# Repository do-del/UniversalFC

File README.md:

# UniversalFC
自制的一些通用航模组件
目前已添加基于STC单片机的无刷电调PCB设计文件，还在打样验证中。

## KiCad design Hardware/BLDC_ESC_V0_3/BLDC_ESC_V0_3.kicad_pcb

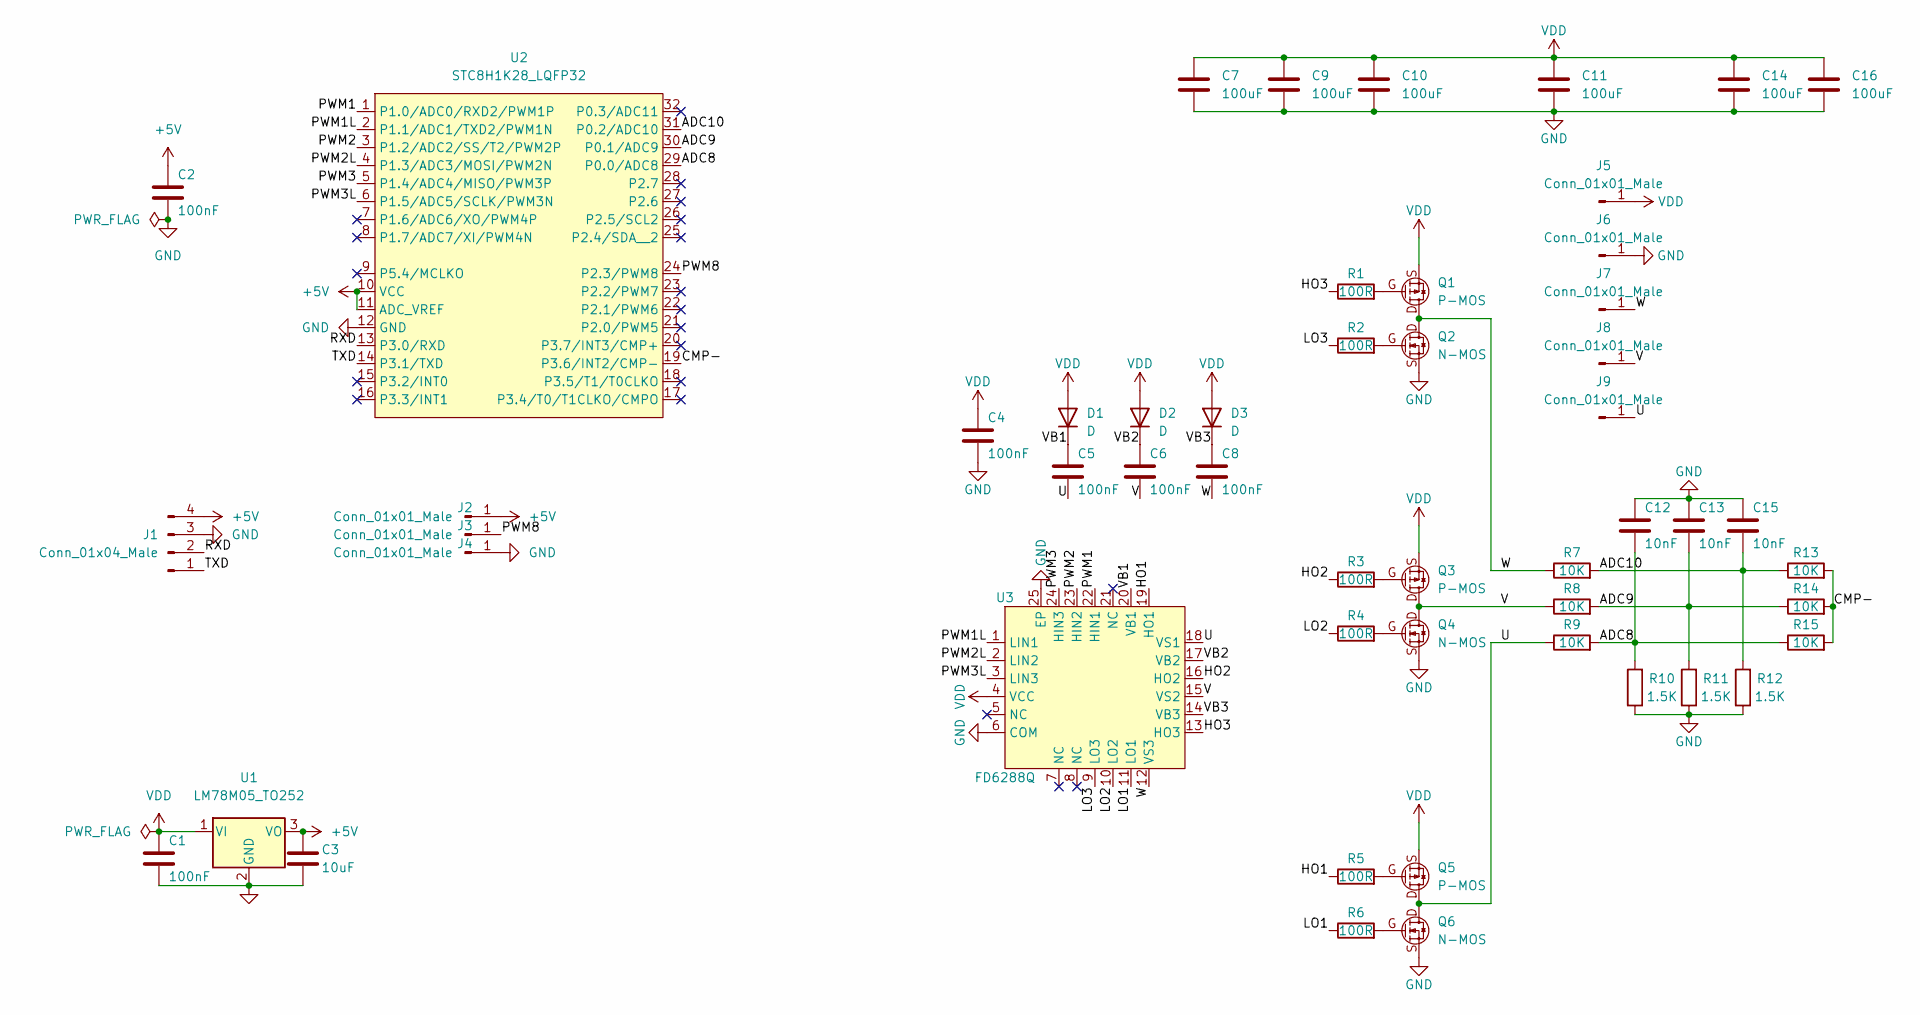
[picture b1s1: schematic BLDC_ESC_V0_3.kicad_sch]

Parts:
C1, C2, C4, C5, C6, C8: 100nF; C_0603_1608Metric_Pad1.08x0.95mm_HandSolder
C3: 10uF; C_0603_1608Metric_Pad1.08x0.95mm_HandSolder
C7, C9, C10, C11, C14, C16: 100uF; C_1210_3225Metric
C12, C13, C15: 10nF; C_0603_1608Metric_Pad1.08x0.95mm_HandSolder
D1, D2, D3: D; D_SOD-323_HandSoldering
J1: Conn_01x04_Male; SH1.0mm_4P_WT
J2, J3, J4, J5, J6, J7, J8, J9: Conn_01x01_Male; PAD_RECT
Q1, Q3, Q5: P-MOS; DFN_3x3_MOS
Q2, Q4, Q6: N-MOS; DFN_3x3_MOS
R1, R2, R3, R4, R5, R6: 100R; R_0603_1608Metric_Pad0.98x0.95mm_HandSolder
R7, R8, R9, R13, R14, R15: 10K; R_0603_1608Metric_Pad0.98x0.95mm_HandSolder
R10, R11, R12: 1.5K; R_0603_1608Metric_Pad0.98x0.95mm_HandSolder
U1: LM78M05_TO252; SOT-89-3
U2: STC8H1K28_LQFP32; QFN-32-1EP_4x4mm_P0.4mm_EP2.65x2.65mm
U3: FD6288Q; QFN-24-1EP_4x4mm_P0.5mm_EP2.6x2.6mm

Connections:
+5V: C2.1, C3.1, J1.4, J2.1, U1.3 (VO), U2.10 (VCC), U2.11 (ADC_VREF)
/ADC8: C12.2, R9.2, R10.2, R15.1, U2.29 (P0.0/ADC8)
/ADC9: C13.2, R8.2, R11.2, R14.1, U2.30 (P0.1/ADC9)
/ADC10: C15.2, R7.2, R12.2, R13.1, U2.31 (P0.2/ADC10)
/CMP-: R13.2, R14.2, R15.2, U2.19 (P3.6/INT2/CMP-)
/HO1: R5.1, U3.19 (HO1)
/HO2: R3.1, U3.16 (HO2)
/HO3: R1.1, U3.13 (HO3)
/LO1: R6.1, U3.11 (LO1)
/LO2: R4.1, U3.10 (LO2)
/LO3: R2.1, U3.9 (LO3)
/PWM1: U2.1 (P1.0/ADC0/RXD2/PWM1P), U3.22 (HIN1)
/PWM1L: U2.2 (P1.1/ADC1/TXD2/PWM1N), U3.1 (LIN1)
/PWM2: U2.3 (P1.2/ADC2/SS/T2/PWM2P), U3.23 (HIN2)
/PWM2L: U2.4 (P1.3/ADC3/MOSI/PWM2N), U3.2 (LIN2)
/PWM3: U2.5 (P1.4/ADC4/MISO/PWM3P), U3.24 (HIN3)
/PWM3L: U2.6 (P1.5/ADC5/SCLK/PWM3N), U3.3 (LIN3)
/PWM8: J3.1, U2.24 (P2.3/PWM8)
/RXD: J1.2, U2.13 (P3.0/RXD)
/TXD: J1.1, U2.14 (P3.1/TXD)
/U: C5.2, J9.1, Q5.D, Q6.D, R9.1, U3.18 (VS1)
/V: C6.2, J8.1, Q3.D, Q4.D, R8.1, U3.15 (VS2)
/VB1: C5.1, D1.1 (K), U3.20 (VB1)
/VB2: C6.1, D2.1 (K), U3.17 (VB2)
/VB3: C8.1, D3.1 (K), U3.14 (VB3)
/W: C8.2, J7.1, Q1.D, Q2.D, R7.1, U3.12 (VS3)
GND: C1.2, C2.2, C3.2, C4.2, C7.2, C9.2, C10.2, C11.2, C12.1, C13.1, C14.2, C15.1, C16.2, J1.3, J4.1, J6.1, Q2.S, Q4.S, Q6.S, R10.1, R11.1, R12.1, U1.2 (GND), U2.12 (GND), U3.6 (COM), U3.25 (EP)
unnamed: Q1.G, R1.2
unnamed: Q2.G, R2.2
unnamed: Q3.G, R3.2
unnamed: Q4.G, R4.2
unnamed: Q5.G, R5.2
unnamed: Q6.G, R6.2
VDD: C1.1, C4.1, C7.1, C9.1, C10.1, C11.1, C14.1, C16.1, D1.2 (A), D2.2 (A), D3.2 (A), J5.1, Q1.S, Q3.S, Q5.S, U1.1 (VI), U3.4 (VCC)

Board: 2 copper layers, 52 parts (25 on the bottom side), 34 nets, no tracks yet.

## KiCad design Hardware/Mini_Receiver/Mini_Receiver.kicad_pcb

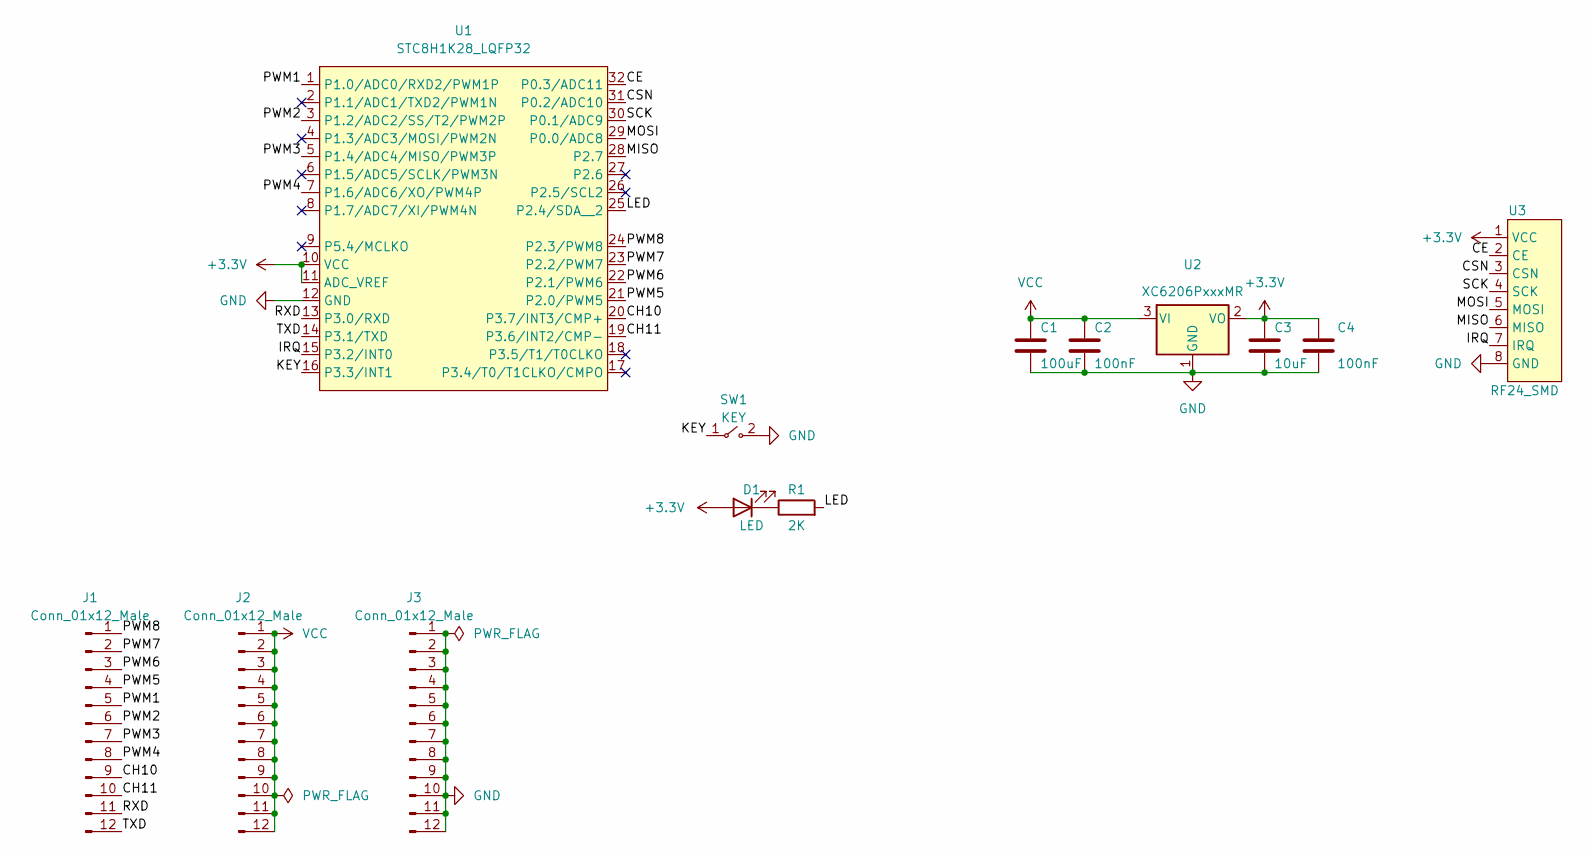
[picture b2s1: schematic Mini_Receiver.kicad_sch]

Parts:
C1: 100uF; C_1210_3225Metric
C2, C4: 100nF; C_0603_1608Metric_Pad1.08x0.95mm_HandSolder
C3: 10uF; C_0603_1608Metric_Pad1.08x0.95mm_HandSolder
D1: LED; LED_0603_1608Metric_Pad1.05x0.95mm_HandSolder
J1, J2, J3: Conn_01x12_Male; PinHeader_1x12_P2.54mm_Vertical
R1: 2K; R_0603_1608Metric_Pad0.98x0.95mm_HandSolder
SW1: KEY; SW_3x4
U1: STC8H1K28_LQFP32; LQFP-32_7x7mm_P0.8mm
U2: XC6206PxxxMR; SOT-23
U3: RF24_SMD

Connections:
+3V3: C3.1, C4.1, D1.2 (A), U1.10 (VCC), U1.11 (ADC_VREF), U2.2 (VO), U3.1 (VCC)
/CE: U1.32 (P0.3/ADC11), U3.2 (CE)
/CH10: J1.9, U1.20 (P3.7/INT3/CMP+)
/CH11: J1.10, U1.19 (P3.6/INT2/CMP-)
/CSN: U1.31 (P0.2/ADC10), U3.3 (CSN)
/IRQ: U1.15 (P3.2/INT0), U3.7 (IRQ)
/KEY: SW1.1 (A), U1.16 (P3.3/INT1)
/LED: R1.2, U1.25 (P2.4/SDA__2)
/MISO: U1.28 (P2.7), U3.6 (MISO)
/MOSI: U1.29 (P0.0/ADC8), U3.5 (MOSI)
/PWM1: J1.5, U1.1 (P1.0/ADC0/RXD2/PWM1P)
/PWM2: J1.6, U1.3 (P1.2/ADC2/SS/T2/PWM2P)
/PWM3: J1.7, U1.5 (P1.4/ADC4/MISO/PWM3P)
/PWM4: J1.8, U1.7 (P1.6/ADC6/XO/PWM4P)
/PWM5: J1.4, U1.21 (P2.0/PWM5)
/PWM6: J1.3, U1.22 (P2.1/PWM6)
/PWM7: J1.2, U1.23 (P2.2/PWM7)
/PWM8: J1.1, U1.24 (P2.3/PWM8)
/RXD: J1.11, U1.13 (P3.0/RXD)
/SCK: U1.30 (P0.1/ADC9), U3.4 (SCK)
/TXD: J1.12, U1.14 (P3.1/TXD)
GND: C1.2, C2.2, C3.2, C4.2, J3.1, J3.2, J3.3, J3.4, J3.5, J3.6, J3.7, J3.8, J3.9, J3.10, J3.11, J3.12, SW1.2 (B), U1.12 (GND), U2.1 (GND), U3.8 (GND)
unnamed: D1.1 (K), R1.1
VCC: C1.1, C2.1, J2.1, J2.2, J2.3, J2.4, J2.5, J2.6, J2.7, J2.8, J2.9, J2.10, J2.11, J2.12, U2.3 (VI)

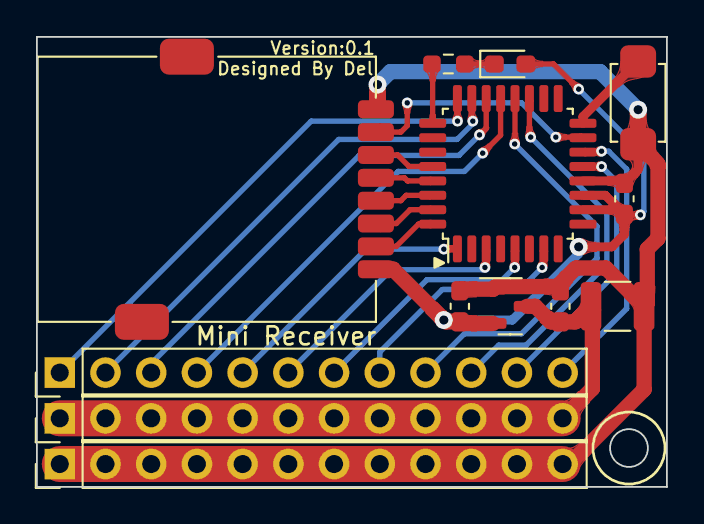
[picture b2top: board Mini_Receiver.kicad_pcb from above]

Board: 2 copper layers, 35.0 x 25.0 mm, 13 parts (0 on the bottom side), 24 nets.

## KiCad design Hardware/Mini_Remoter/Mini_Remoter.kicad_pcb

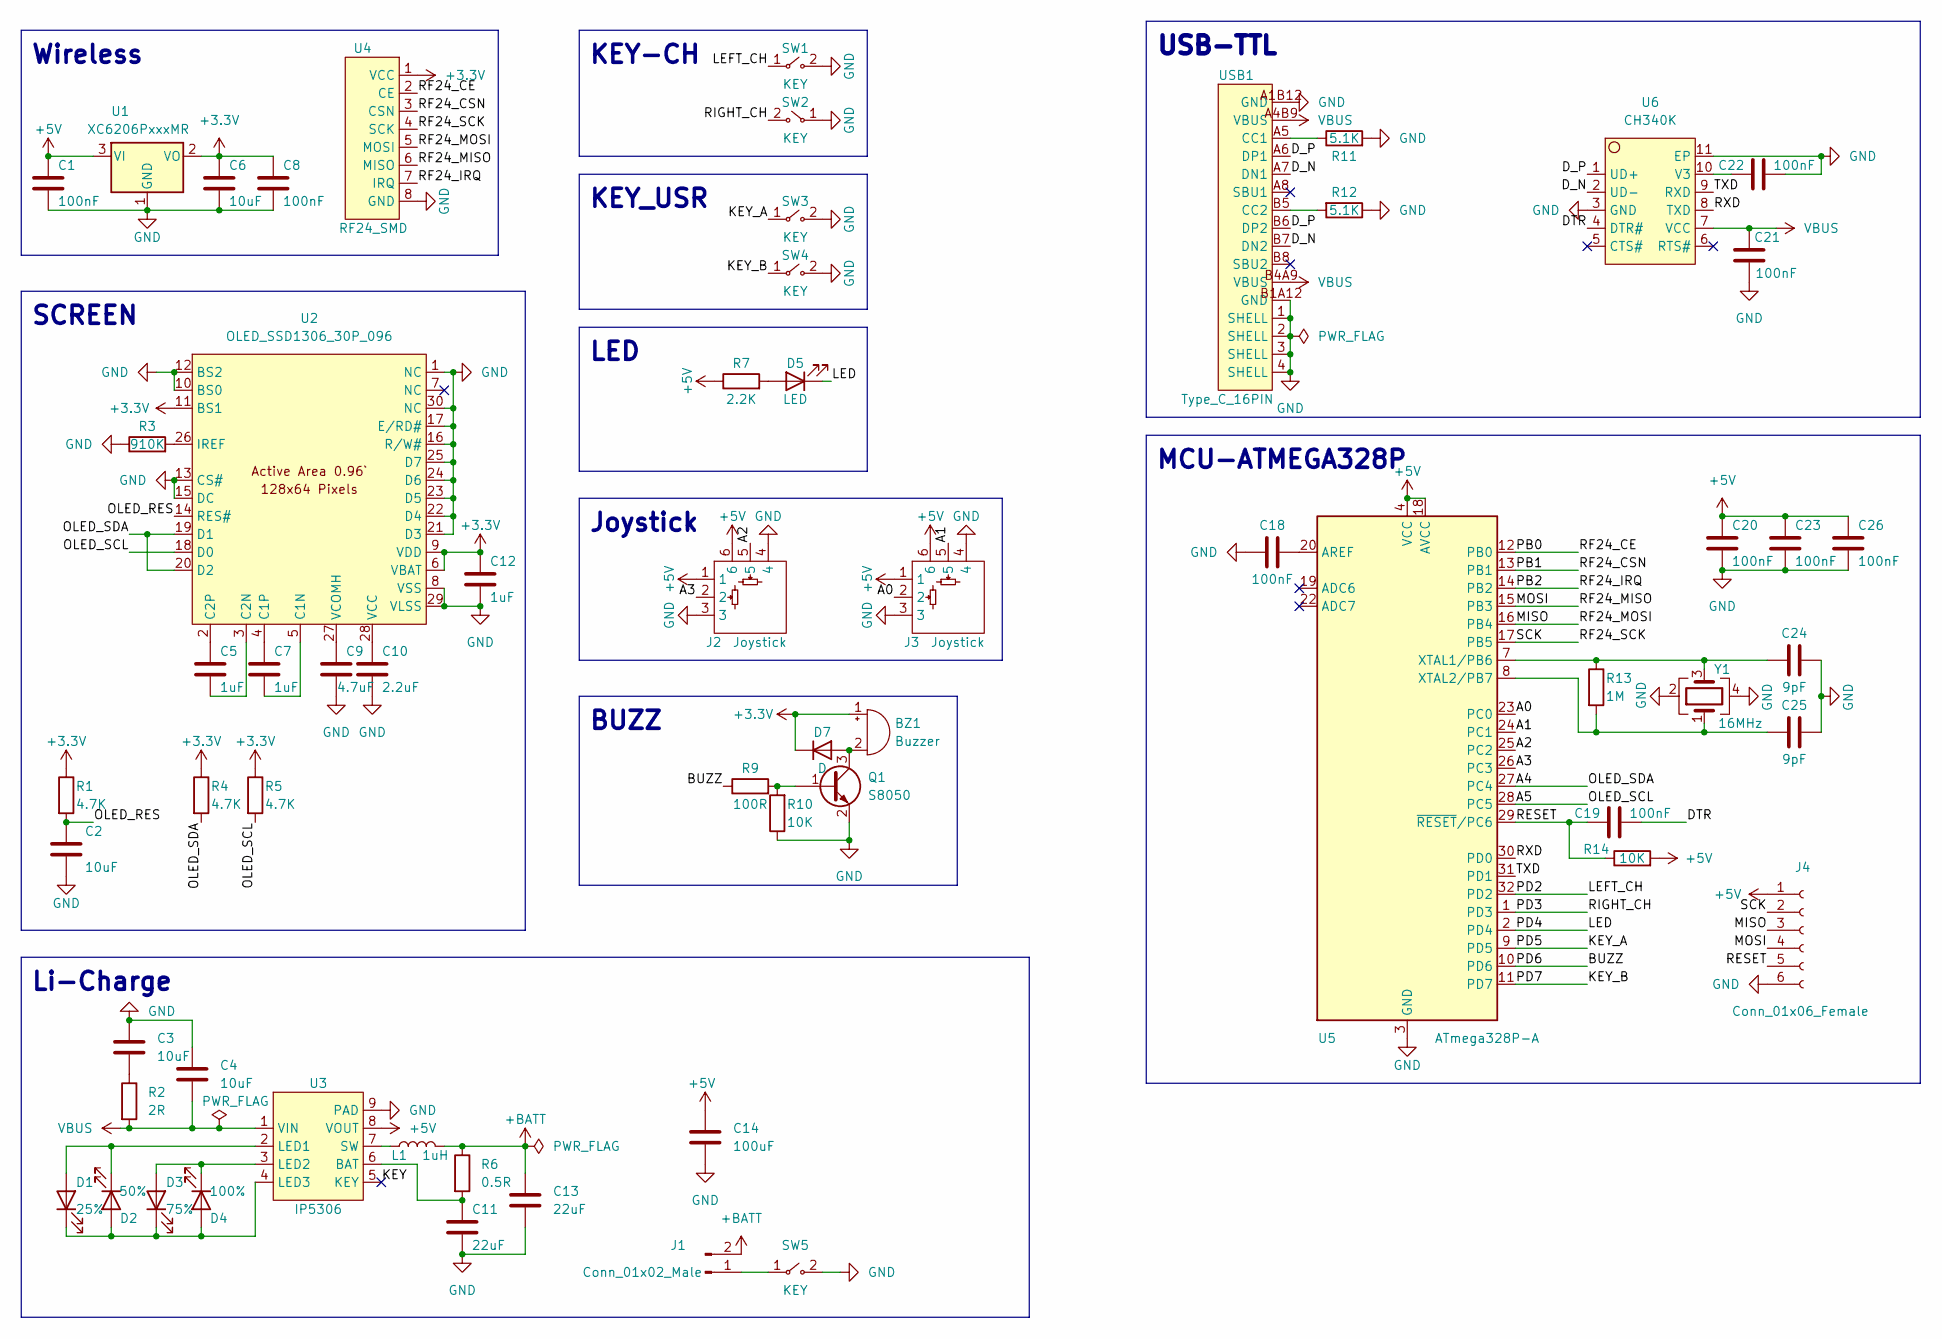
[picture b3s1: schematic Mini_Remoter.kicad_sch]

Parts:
BZ1: Buzzer; DET402
C1, C8, C18, C19, C20, C21, C22, C23, C26: 100nF; C_0603_1608Metric_Pad1.08x0.95mm_HandSolder
C2, C3, C4, C6: 10uF; C_0603_1608Metric_Pad1.08x0.95mm_HandSolder
C5, C7, C12: 1uF; C_0603_1608Metric_Pad1.08x0.95mm_HandSolder
C9: 4.7uF; C_0603_1608Metric_Pad1.08x0.95mm_HandSolder
C10: 2.2uF; C_0603_1608Metric_Pad1.08x0.95mm_HandSolder
C11, C13: 22uF; C_1206_3216Metric
C14: 100uF; C_1210_3225Metric
C24, C25: 9pF; C_0603_1608Metric_Pad1.08x0.95mm_HandSolder
D1: 25%; LED_0603_1608Metric_Pad1.05x0.95mm_HandSolder
D2: 50%; LED_0603_1608Metric_Pad1.05x0.95mm_HandSolder
D3: 75%; LED_0603_1608Metric_Pad1.05x0.95mm_HandSolder
D4: 100%; LED_0603_1608Metric_Pad1.05x0.95mm_HandSolder
D5: LED; LED_0603_1608Metric_Pad1.05x0.95mm_HandSolder
D7: D; D_SOD-123
J1: Conn_01x02_Male; PH2.0mm-2P-WT
J2, J3: Joystick; PSP_JOYSTICK
J4: Conn_01x06_Female; JST_SHL_SM06B-SHLS-TF_1x06-1MP_P1.00mm_Horizontal
L1: 1uH; IND0420
Q1: S8050; SOT-23
R1, R4, R5: 4.7K; R_0603_1608Metric_Pad0.98x0.95mm_HandSolder
R2: 2R; R_0603_1608Metric_Pad0.98x0.95mm_HandSolder
R3: 910K; R_0603_1608Metric_Pad0.98x0.95mm_HandSolder
R6: 0.5R; R_0603_1608Metric_Pad0.98x0.95mm_HandSolder
R7: 2.2K; R_0603_1608Metric_Pad0.98x0.95mm_HandSolder
R9: 100R; R_0603_1608Metric_Pad0.98x0.95mm_HandSolder
R10, R14: 10K; R_0603_1608Metric_Pad0.98x0.95mm_HandSolder
R11, R12: 5.1K; R_0603_1608Metric_Pad0.98x0.95mm_HandSolder
R13: 1M; R_0603_1608Metric_Pad0.98x0.95mm_HandSolder
SW1, SW2: KEY; SW_2x4x3.5_SIDE
SW3, SW4: KEY; BUTTON_SWITCH_4x4
SW5: KEY; SELFLOCK_SWITCH
U1: XC6206PxxxMR; SOT-23
U2: OLED_SSD1306_30P_096; OLED_12864_30P_P0.7_HOLE
U3: IP5306; HSOP-8-1EP_3.9x4.9mm_P1.27mm_EP2.3x2.3mm
U4: RF24_SMD
U5: ATmega328P-A; TQFP-32_7x7mm_P0.8mm
U6: CH340K; ESSOP-10_P1.0_3.9
USB1: Type_C_16PIN; TYPE-C-16PIN_SMD
Y1: 16MHz; Crystal_SMD_3225-4Pin_3.2x2.5mm

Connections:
+3V3: BZ1.1 (-), C6.1, C8.1, C12.2, D7.1 (K), R1.1, R4.1, R5.1, U1.2 (VO), U2.6 (VBAT), U2.9 (VDD), U2.11 (BS1), U4.1 (VCC)
+5V: C1.1, C14.1, C20.1, C23.1, C26.1, J2.1, J2.6, J3.1, J3.6, J4.1, R7.1, R14.2, U1.3 (VI), U3.8 (VOUT), U5.4 (VCC), U5.6 (VCC), U5.18 (AVCC)
+BATT: C13.1, J1.2, L1.2, R6.1
/A0: J3.2, U5.23 (PC0)
/A1: J3.5, U5.24 (PC1)
/A2: J2.5, U5.25 (PC2)
/A3: J2.2, U5.26 (PC3)
/A4: R4.2, U2.19 (D1), U2.20 (D2), U5.27 (PC4)
/A5: R5.2, U2.18 (D0), U5.28 (PC5)
/BUZZ: R9.1, U5.10 (PD6)
/DTR: C19.1, U6.4 (DTR#)
/D_N: U6.2 (UD-), USB1.A7 (DN1), USB1.B7 (DN2)
/D_P: U6.1 (UD+), USB1.A6 (DP1), USB1.B6 (DP2)
/KEY: U3.5 (KEY)
/KEY_A: SW3.1 (A), U5.9 (PD5)
/LED: D5.1 (K), U5.2 (PD4)
/LEFT_CH: SW1.1 (A), U5.32 (PD2)
/MISO: J4.3, U4.5 (MOSI), U5.16 (PB4)
/MOSI: J4.4, U4.6 (MISO), U5.15 (PB3)
/OLED_RES: C2.1, R1.2, U2.14 (RES#)
/PB0: U4.2 (CE), U5.12 (PB0)
/PB1: U4.3 (CSN), U5.13 (PB1)
/PD3: SW2.2 (B), U5.1 (PD3)
/PD7: SW4.1 (A), U5.11 (PD7)
/RESET: C19.2, J4.5, R14.1, U5.29 (~RESET/PC6)
/RF24_IRQ: U4.7 (IRQ), U5.14 (PB2)
/RF24_SCK: J4.2, U4.4 (SCK), U5.17 (PB5)
/RXD: U5.30 (PD0), U6.8 (TXD)
/TXD: U5.31 (PD1), U6.9 (RXD)
GND: C1.2, C2.2, C3.1, C4.1, C6.2, C8.2, C9.1, C10.1, C11.2, C12.1, C13.2, C14.2, C18.1, C20.2, C21.1, C22.1, C23.2, C24.2, C25.2, C26.2, J2.3, J2.4, J3.3, J3.4, J4.6, Q1.2 (E), R3.1, R10.1, R11.2, R12.1, SW1.2 (B), SW2.1 (A), SW3.2 (B), SW4.2 (B), SW5.2 (B), U1.1 (GND), U2.1 (NC), U2.8 (VSS), U2.10 (BS0), U2.12 (BS2), U2.13 (CS#), U2.15 (DC), U2.16 (R/W#), U2.17 (E/RD#), U2.21 (D3), U2.22 (D4), U2.23 (D5), U2.24 (D6), U2.25 (D7), U2.29 (VLSS), U2.30 (NC), U3.9 (PAD), U4.8 (GND), U5.3 (GND), U5.5 (GND), U5.21 (GND), U6.3 (GND), U6.11 (EP), USB1.1 (SHELL), USB1.2 (SHELL), USB1.3 (SHELL), USB1.4 (SHELL), USB1.A1B12 (GND), USB1.B1A12 (GND), Y1.2, Y1.4
unnamed: BZ1.2 (+), D7.2 (A), Q1.3 (C)
unnamed: C3.2, R2.1
unnamed: C5.1, U2.3 (C2N)
unnamed: C5.2, U2.2 (C2P)
unnamed: C7.1, U2.5 (C1N)
unnamed: C7.2, U2.4 (C1P)
unnamed: C9.2, U2.27 (VCOMH)
unnamed: C10.2, U2.28 (VCC)
unnamed: C11.1, R6.2, U3.6 (BAT)
unnamed: C18.2, U5.20 (AREF)
unnamed: C22.2, U6.10 (V3)
unnamed: C24.1, R13.1, U5.7 (XTAL1/PB6), Y1.3
unnamed: C25.1, R13.2, U5.8 (XTAL2/PB7), Y1.1
unnamed: D1.1 (K), D2.2 (A), D3.1 (K), D4.2 (A), U3.4 (LED3)
unnamed: D1.2 (A), D2.1 (K), U3.2 (LED1)
unnamed: D3.2 (A), D4.1 (K), U3.3 (LED2)
unnamed: D5.2 (A), R7.2
unnamed: J1.1, SW5.1 (A)
unnamed: L1.1, U3.7 (SW)
unnamed: Q1.1 (B), R9.2, R10.2
unnamed: R3.2, U2.26 (IREF)
unnamed: R11.1, USB1.A5 (CC1)
unnamed: R12.2, USB1.B5 (CC2)
VBUS: C4.2, C21.2, R2.2, U3.1 (VIN), U6.7 (VCC), USB1.A4B9 (VBUS), USB1.B4A9 (VBUS)

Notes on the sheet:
MCU-ATMEGA328P
USB-TTL
Joystick
Li-Charge
KEY_USR
KEY-CH
LED
SCREEN
BUZZ
Wireless

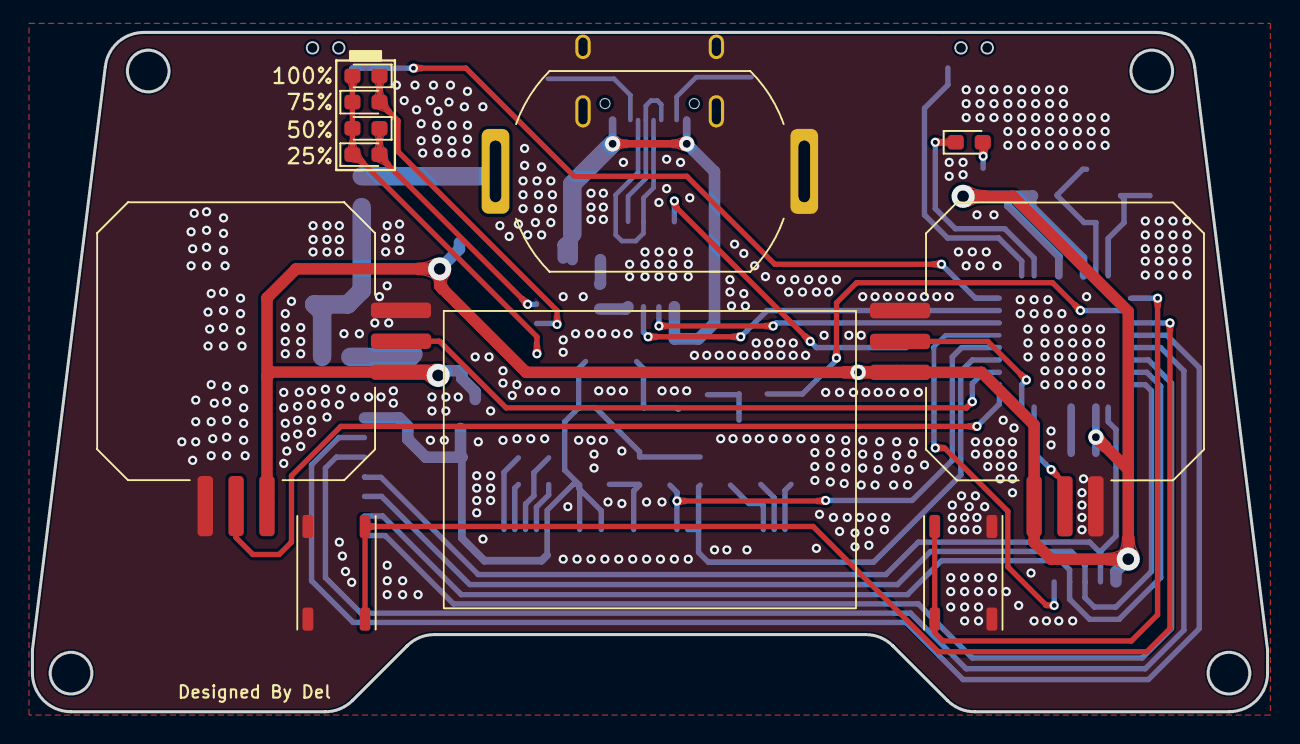
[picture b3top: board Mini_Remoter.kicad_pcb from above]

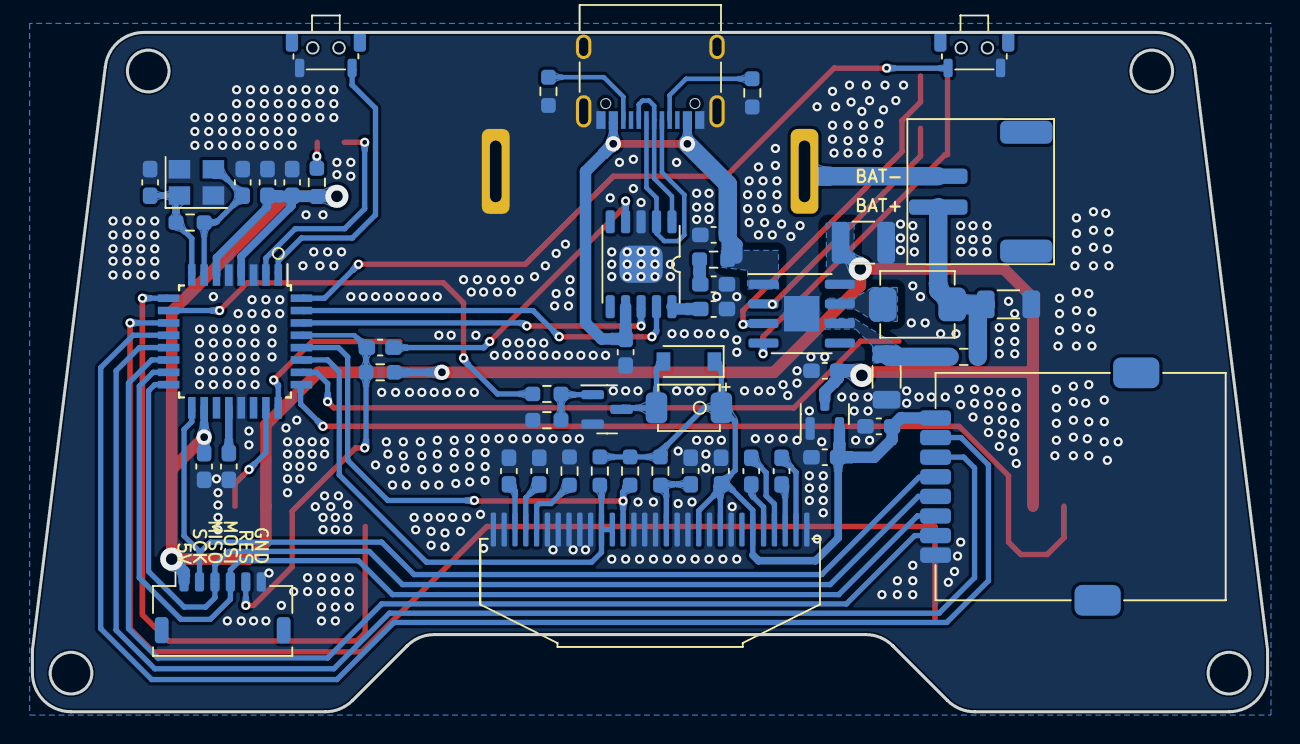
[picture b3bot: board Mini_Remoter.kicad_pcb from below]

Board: 2 copper layers, 80.0 x 44.0 mm, 62 parts (51 on the bottom side), 53 nets.

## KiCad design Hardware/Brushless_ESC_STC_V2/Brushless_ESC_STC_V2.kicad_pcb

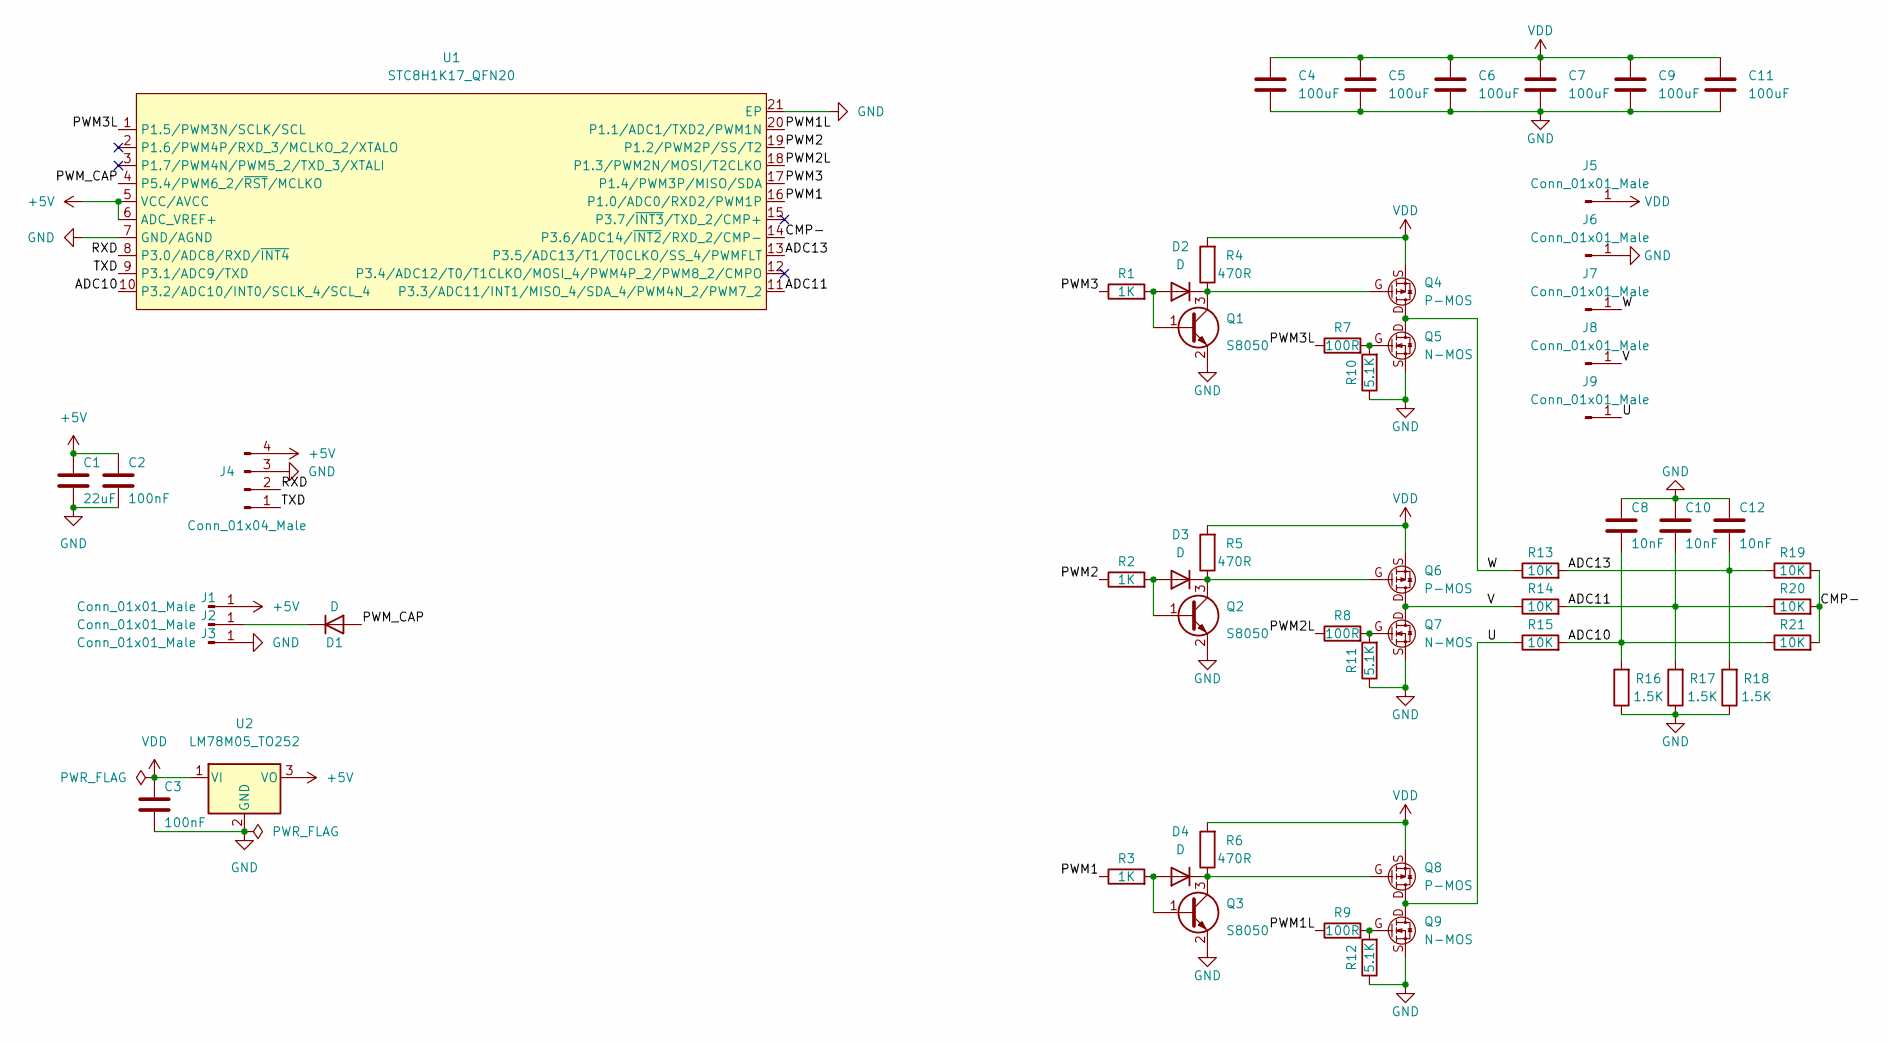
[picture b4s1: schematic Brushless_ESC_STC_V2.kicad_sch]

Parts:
C1: 22uF; C_1206_3216Metric
C2, C3: 100nF; C_0603_1608Metric_Pad1.08x0.95mm_HandSolder
C4, C5, C6, C7, C9, C11: 100uF; C_1210_3225Metric
C8, C10, C12: 10nF; C_0603_1608Metric_Pad1.08x0.95mm_HandSolder
D1, D2, D3, D4: D; D_SOD-123
J1, J2, J3, J5, J6, J7, J8, J9: Conn_01x01_Male; PAD_RECT
J4: Conn_01x04_Male; SH1.0mm_4P_WT
Q1, Q2, Q3: S8050; SOT-23
Q4, Q6, Q8: P-MOS; P-MOS-TO-252-2
Q5, Q7, Q9: N-MOS; N-MOS-TO-252-2
R1, R2, R3: 1K; R_0603_1608Metric_Pad0.98x0.95mm_HandSolder
R4, R5, R6: 470R; R_0603_1608Metric_Pad0.98x0.95mm_HandSolder
R7, R8, R9: 100R; R_0603_1608Metric_Pad0.98x0.95mm_HandSolder
R10, R11, R12: 5.1K; R_0603_1608Metric_Pad0.98x0.95mm_HandSolder
R13, R14, R15, R19, R20, R21: 10K; R_0603_1608Metric_Pad0.98x0.95mm_HandSolder
R16, R17, R18: 1.5K; R_0603_1608Metric_Pad0.98x0.95mm_HandSolder
U1: STC8H1K17_QFN20; QFN-20-1EP_3x3mm_P0.4mm_EP1.65x1.65mm
U2: LM78M05_TO252; TO-252-2

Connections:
+5V: C1.1, C2.1, J1.1, J4.4, U1.5 (VCC/AVCC), U1.6 (ADC_VREF+), U2.3 (VO)
/ADC10: C8.2, R15.2, R16.2, R21.1, U1.10 (P3.2/ADC10/INT0/SCLK_4/SCL_4)
/ADC11: C10.2, R14.2, R17.2, R20.1, U1.11 (P3.3/ADC11/INT1/MISO_4/SDA_4/PWM4N_2/PW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)
/ADC13: C12.2, R13.2, R18.2, R19.1, U1.13 (P3.5/ADC13/T1/T0CLKO/SS_4/PWMFLT)
/CMP-: R19.2, R20.2, R21.2, U1.14 (P3.6/ADC14/~INT2/RXD_2/CMP-)
/PWM1: R3.1, U1.16 (P1.0/ADC0/RXD2/PWM1P)
/PWM1L: R9.1, U1.20 (P1.1/ADC1/TXD2/PWM1N)
/PWM2: R2.1, U1.19 (P1.2/PWM2P/SS/T2)
/PWM2L: R8.1, U1.18 (P1.3/PWM2N/MOSI/T2CLKO)
/PWM3: R1.1, U1.17 (P1.4/PWM3P/MISO/SDA)
/PWM3L: R7.1, U1.1 (P1.5/PWM3N/SCLK/SCL)
/PWM_CAP: D1.2 (A), U1.4 (P5.4/PWM6_2/~RST/MCLKO)
/RXD: J4.2, U1.8 (P3.0/ADC8/RXD/~INT4)
/TXD: J4.1, U1.9 (P3.1/ADC9/TXD)
/U: J9.1, Q8.D, Q9.D, R15.1
/V: J8.1, Q6.D, Q7.D, R14.1
/W: J7.1, Q4.D, Q5.D, R13.1
GND: C1.2, C2.2, C3.2, C4.2, C5.2, C6.2, C7.2, C8.1, C9.2, C10.1, C11.2, C12.1, J3.1, J4.0, J4.3, J6.1, Q1.2 (E), Q2.2 (E), Q3.2 (E), Q5.S, Q7.S, Q9.S, R10.1, R11.1, R12.1, R16.1, R17.1, R18.1, U1.7 (GND/AGND), U1.21 (EP), U2.2 (GND)
unnamed: D2.1 (K), Q1.3 (C), Q4.G, R4.1
unnamed: D2.2 (A), Q1.1 (B), R1.2
unnamed: D3.1 (K), Q2.3 (C), Q6.G, R5.1
unnamed: D3.2 (A), Q2.1 (B), R2.2
unnamed: D4.1 (K), Q3.3 (C), Q8.G, R6.1
unnamed: D4.2 (A), Q3.1 (B), R3.2
unnamed: D1.1 (K), J2.1
unnamed: Q5.G, R7.2, R10.2
unnamed: Q7.G, R8.2, R11.2
unnamed: Q9.G, R9.2, R12.2
VDD: C3.1, C4.1, C5.1, C6.1, C7.1, C9.1, C11.1, J5.1, Q4.S, Q6.S, Q8.S, R4.2, R5.2, R6.2, U2.1 (VI)

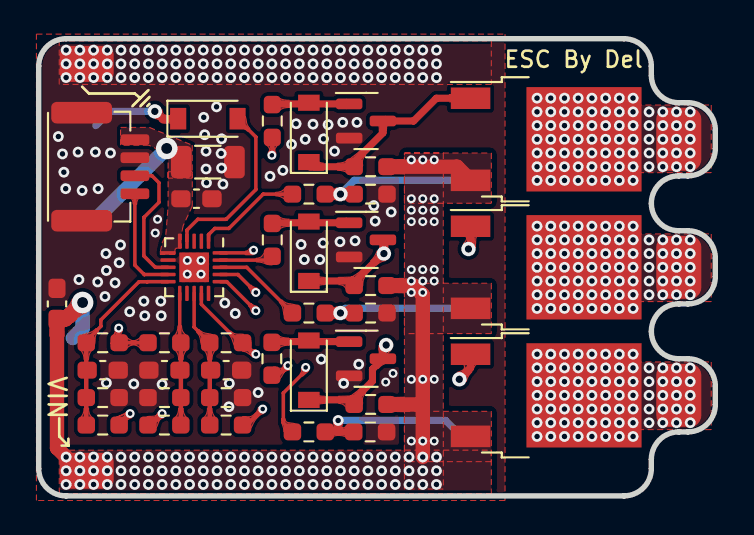
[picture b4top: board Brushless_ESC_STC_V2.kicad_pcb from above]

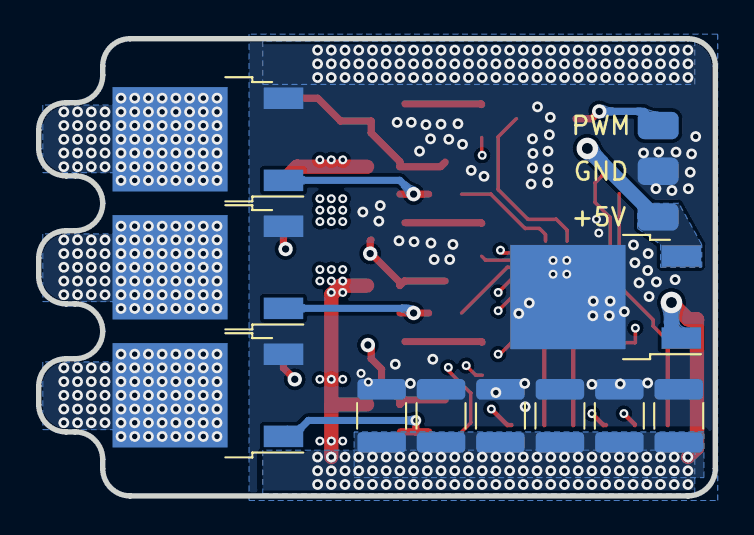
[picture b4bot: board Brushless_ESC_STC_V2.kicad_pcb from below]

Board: 4 copper layers, 37.6 x 25.4 mm, 57 parts (13 on the bottom side), 29 nets.

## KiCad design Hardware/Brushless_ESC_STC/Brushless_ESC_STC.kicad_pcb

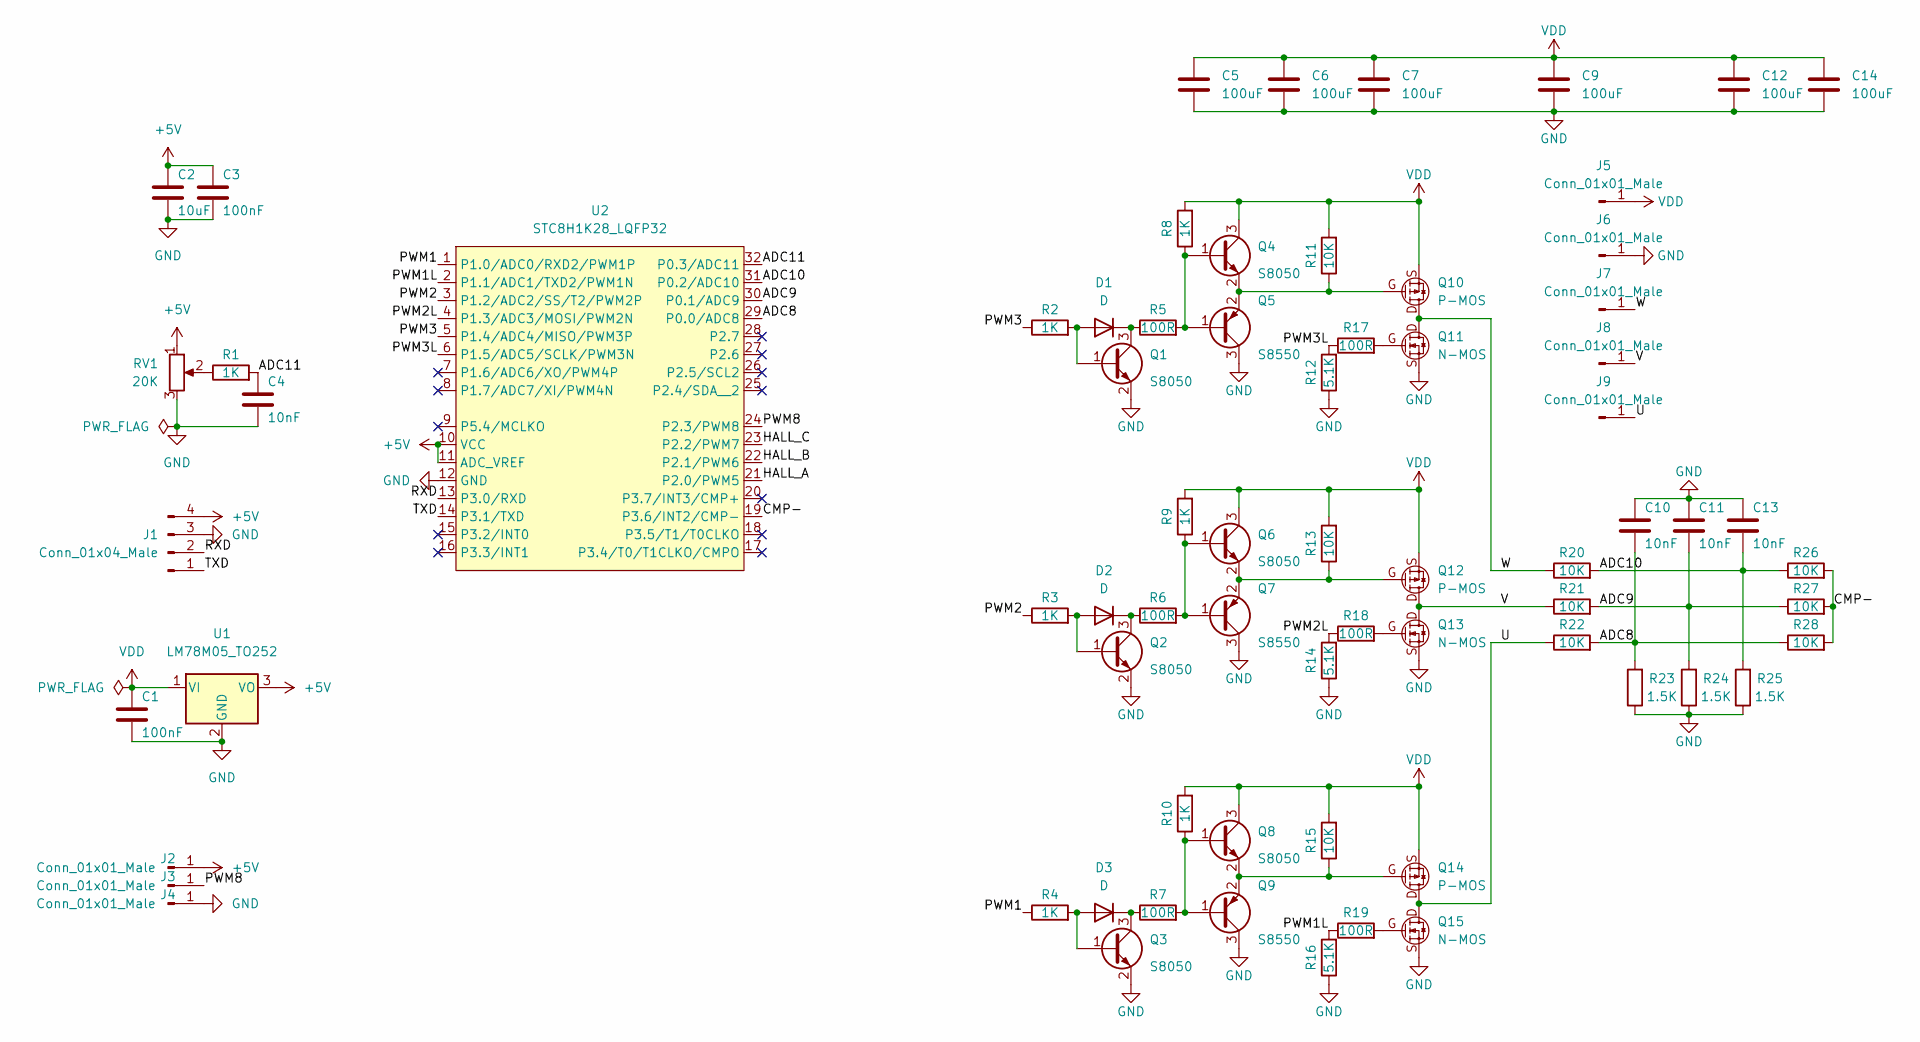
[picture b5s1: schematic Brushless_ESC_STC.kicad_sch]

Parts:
C1, C3: 100nF; C_0603_1608Metric_Pad1.08x0.95mm_HandSolder
C2: 10uF; C_1206_3216Metric
C4, C10, C11, C13: 10nF; C_0603_1608Metric_Pad1.08x0.95mm_HandSolder
C5, C6, C7, C9, C12, C14: 100uF; C_1210_3225Metric
D1, D2, D3: D; D_SOD-123
J1: Conn_01x04_Male; SH1.0mm_4P_WT
J2, J3, J4, J5, J6, J7, J8, J9: Conn_01x01_Male; PAD_RECT
Q1, Q2, Q3, Q4, Q6, Q8: S8050; SOT-23
Q5, Q7, Q9: S8550; SOT-23
Q10, Q12, Q14: P-MOS; P-MOS-TO-252-2
Q11, Q13, Q15: N-MOS; N-MOS-TO-252-2
R1, R2, R3, R4, R8, R9, R10: 1K; R_0603_1608Metric_Pad0.98x0.95mm_HandSolder
R5, R6, R7, R17, R18, R19: 100R; R_0603_1608Metric_Pad0.98x0.95mm_HandSolder
R11, R13, R15, R20, R21, R22, R26, R27, R28: 10K; R_0603_1608Metric_Pad0.98x0.95mm_HandSolder
R12, R14, R16: 5.1K; R_0603_1608Metric_Pad0.98x0.95mm_HandSolder
R23, R24, R25: 1.5K; R_0603_1608Metric_Pad0.98x0.95mm_HandSolder
RV1: 20K; Potentiometer_Bourns_3314J_Vertical
U1: LM78M05_TO252; TO-252-2
U2: STC8H1K28_LQFP32; LQFP-32_7x7mm_P0.8mm

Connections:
+5V: C2.1, C3.1, J1.4, J2.1, RV1.1, U1.3 (VO), U2.10 (VCC), U2.11 (ADC_VREF)
/ADC8: C10.2, R22.2, R23.2, R28.1, U2.29 (P0.0/ADC8)
/ADC9: C11.2, R21.2, R24.2, R27.1, U2.30 (P0.1/ADC9)
/ADC10: C13.2, R20.2, R25.2, R26.1, U2.31 (P0.2/ADC10)
/ADC11: C4.1, R1.2, U2.32 (P0.3/ADC11)
/CMP-: R26.2, R27.2, R28.2, U2.19 (P3.6/INT2/CMP-)
/HALL_A: U2.21 (P2.0/PWM5)
/HALL_B: U2.22 (P2.1/PWM6)
/HALL_C: U2.23 (P2.2/PWM7)
/PWM1: R4.1, U2.1 (P1.0/ADC0/RXD2/PWM1P)
/PWM1L: R16.2, R19.1, U2.2 (P1.1/ADC1/TXD2/PWM1N)
/PWM2: R3.1, U2.3 (P1.2/ADC2/SS/T2/PWM2P)
/PWM2L: R14.2, R18.1, U2.4 (P1.3/ADC3/MOSI/PWM2N)
/PWM3: R2.1, U2.5 (P1.4/ADC4/MISO/PWM3P)
/PWM3L: R12.2, R17.1, U2.6 (P1.5/ADC5/SCLK/PWM3N)
/PWM8: J3.1, U2.24 (P2.3/PWM8)
/RXD: J1.2, U2.13 (P3.0/RXD)
/TXD: J1.1, U2.14 (P3.1/TXD)
/U: J9.1, Q14.D, Q15.D, R22.1
/V: J8.1, Q12.D, Q13.D, R21.1
/W: J7.1, Q10.D, Q11.D, R20.1
GND: C1.2, C2.2, C3.2, C4.2, C5.2, C6.2, C7.2, C9.2, C10.1, C11.1, C12.2, C13.1, C14.2, J1.0, J1.3, J4.1, J6.1, Q1.2 (E), Q2.2 (E), Q3.2 (E), Q5.3 (C), Q7.3 (C), Q9.3 (C), Q11.S, Q13.S, Q15.S, R12.1, R14.1, R16.1, R23.1, R24.1, R25.1, RV1.3, U1.2 (GND), U2.12 (GND)
unnamed: D1.1 (K), Q1.3 (C), R5.1
unnamed: D1.2 (A), Q1.1 (B), R2.2
unnamed: D2.1 (K), Q2.3 (C), R6.1
unnamed: D2.2 (A), Q2.1 (B), R3.2
unnamed: D3.1 (K), Q3.3 (C), R7.1
unnamed: D3.2 (A), Q3.1 (B), R4.2
unnamed: Q4.1 (B), Q5.1 (B), R5.2, R8.1
unnamed: Q6.1 (B), Q7.1 (B), R6.2, R9.1
unnamed: Q8.1 (B), Q9.1 (B), R7.2, R10.1
unnamed: Q4.2 (E), Q5.2 (E), Q10.G, R11.1
unnamed: Q11.G, R17.2
unnamed: Q6.2 (E), Q7.2 (E), Q12.G, R13.1
unnamed: Q13.G, R18.2
unnamed: Q8.2 (E), Q9.2 (E), Q14.G, R15.1
unnamed: Q15.G, R19.2
unnamed: R1.1, RV1.2
VDD: C1.1, C5.1, C6.1, C7.1, C9.1, C12.1, C14.1, J5.1, Q4.3 (C), Q6.3 (C), Q8.3 (C), Q10.S, Q12.S, Q14.S, R8.2, R9.2, R10.2, R11.2, R13.2, R15.2, U1.1 (VI)

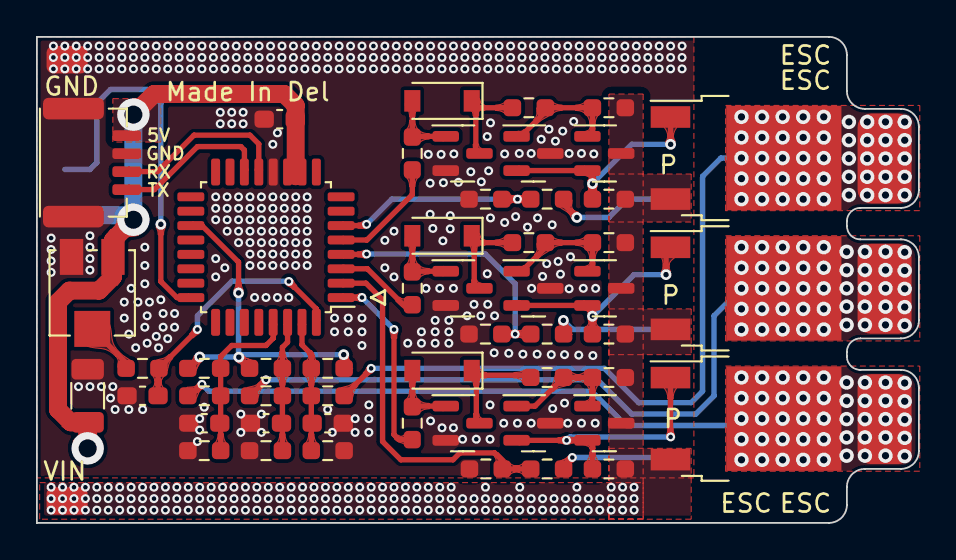
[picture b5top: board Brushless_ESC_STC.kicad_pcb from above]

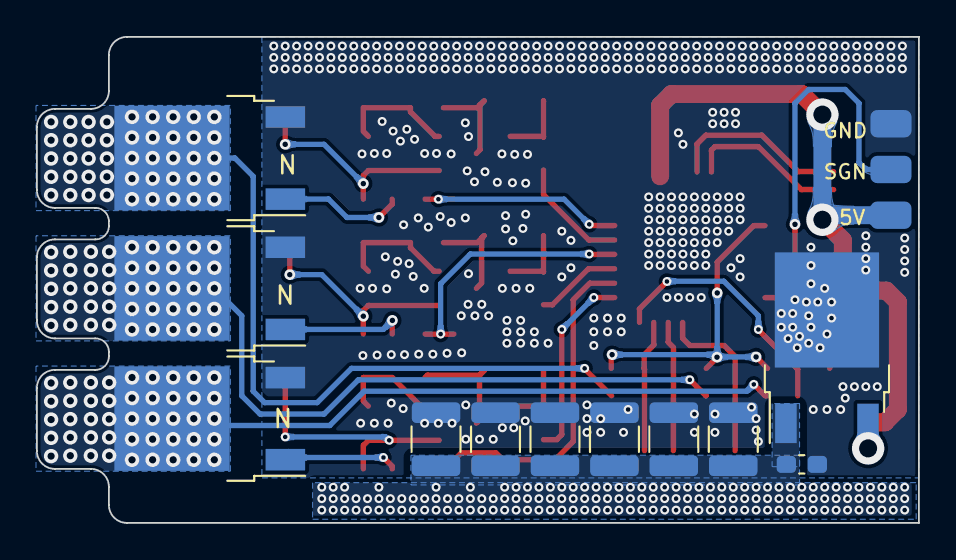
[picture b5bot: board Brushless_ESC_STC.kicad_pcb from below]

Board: 2 copper layers, 49.0 x 27.0 mm, 71 parts (14 on the bottom side), 36 nets.
